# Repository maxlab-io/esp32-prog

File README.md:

# esp32-prog

A compact USB‑C programmer for flashing and debugging ESP32‑based boards over UART, designed to connect to the target through a [Tag‑Connect TC2050‑IDC](https://www.tag-connect.com/product/tc2050-idc-tag-connect-2050-idc) cable so the target board needs no programming header at all.

Plug it into USB, press the Tag‑Connect onto the target, and flash with `esptool`, ESP‑IDF, Arduino or PlatformIO. The on‑board auto‑reset circuit puts the ESP32 into download mode automatically, with no BOOT/EN buttons to press.

## Features

- **USB‑C** (USB 2.0) with 5.1 kΩ CC pull‑downs, so it works with both C‑to‑C and A‑to‑C cables
- **CP2102** USB‑to‑UART bridge
- **Automatic boot/reset**: the standard Espressif DTR/RTS cross‑coupled circuit, built with AO3400A MOSFETs
- **Switchable target power**: independent 5 V and 3.3 V outputs, each enabled by a DIP switch
- **3.3 V LDO** (ST LD39200, 2 A class) for powering the target
- **Buffered, back‑power‑safe I/O**: SN74LVC1G125 buffers with I<sub>off</sub> protection, so an unpowered target is not parasitically powered through its UART or strapping pins
- **ESD protection** on VBUS, D+ and D‑, plus a ferrite bead on VBUS
- **Status LEDs** for USB power, 5 V out, 3.3 V present, TX and RX activity
- 2‑layer, 55 × 30 mm board, four M3 mounting holes, all components on the top side

## Connector pinout

The target connector **J2** is a 2×5, 2.54 mm pin header that mates with the 0.1" IDC end of a Tag‑Connect TC2050‑IDC cable. The pinout is also printed on the board silkscreen.

| Pin | Silkscreen | Signal | Direction (from programmer) | Connect to on target |
|----:|:----------:|--------|-----------------------------|----------------------|
| 1 | 5V   | +5V     | Power out (switched)     | 5 V / VIN (optional) |
| 2 | 3V3  | +3.3V   | Power out (switched) / I/O reference | 3V3 rail (**always connect**, see below) |
| 3 | GND  | GND     | n/a                      | GND |
| 4 | GND  | GND     | n/a                      | GND |
| 5 | EN   | ESP_EN  | Open‑drain, pulls low    | `EN` / `CHIP_PU` |
| 6 | BT   | ESP_BOOT| Open‑drain, pulls low    | Boot strapping pin (`GPIO0` on ESP32/S2/S3, `GPIO9` on C3/C6/H2) |
| 7 | RX   | RXD     | Input                    | Target `U0TXD` |
| 8 | TX   | TXD     | Output                   | Target `U0RXD` |
| 9 | NC   | n/a     | Not connected            | n/a |
| 10 | NC  | n/a     | Not connected            | n/a |

TX and RX are named from the programmer's point of view, so they cross over to the target's UART.

### Designing the target‑side footprint

- Use the **TC2050** footprint (the legged version, to match the TC2050‑IDC cable's retaining clips) and assign signals using the pin numbers in the table above.
- **Always route pin 2 to the target's 3.3 V rail**, even if the target has its own supply. The TX, EN and BOOT buffers are powered from this pin, so it sets the output logic level and lets the programmer work with self‑powered targets.
- EN and BOOT are only ever pulled low by the programmer, so the target must provide its own pull‑ups (most ESP32 modules and reference designs already have them).

## Using it

### Power switch and LEDs

The two‑position DIP switch **SW1** (labeled `5V` and `3.3V` on the silkscreen) enables the corresponding output on J2.

| Target situation | 5V | 3.3V |
|------------------|:--:|:----:|
| Target has its own power supply | Off | Off |
| Power the target from the programmer, 3.3 V only | Off | On |
| Power the target from the programmer, through its own 5 V regulator | On | Off |

Do not enable an output when the target is already powered from another source. Both outputs pass through SS34 Schottky diodes to prevent back‑feeding into the programmer, so expect a few hundred millivolts of drop under load.

| LED | Color | Meaning |
|-----|-------|---------|
| D5  | Red   | USB power present |
| D4  | Red   | 5 V output enabled |
| D8  | Red   | 3.3 V present on J2 pin 2 (from the programmer or the target) |
| D9  | Blue  | TX activity |
| D10 | Blue  | RX activity |

### Drivers

Linux supports the CP2102 out of the box (`cp210x` driver), and the programmer shows up as `/dev/ttyUSB*`. On Windows or macOS, if no serial port appears, install the [Silicon Labs CP210x VCP driver](https://www.silabs.com/developer-tools/usb-to-uart-bridge-vcp-drivers).

### Flashing

Because DTR and RTS drive the auto‑reset circuit, any tool that uses esptool's default reset sequence works without touching the target:

```sh
# ESP-IDF
idf.py -p /dev/ttyUSB0 flash monitor

# esptool directly: quick sanity check that the target is reachable
esptool.py --port /dev/ttyUSB0 flash_id
```

Arduino IDE and PlatformIO use esptool under the hood, so selecting the programmer's serial port is all that is needed.

## How it works

1. **USB input.** USB‑C VBUS passes through a ferrite bead (BLM21PG221SN1D). RClamp0521P TVS diodes protect VBUS, D+ and D‑.
2. **USB‑UART.** A CP2102‑GMR, powered from VBUS through its internal regulator, provides TXD/RXD plus the DTR and RTS modem lines.
3. **Auto‑reset.** DTR and RTS are buffered and fed to two cross‑coupled AO3400A N‑MOSFETs, the same topology as on Espressif DevKits. Toggling DTR/RTS pulls EN and BOOT low in the sequence that esptool expects.
4. **Target power.** An LD39200 LDO generates 3.3 V from VBUS. Two AO3401A P‑MOSFETs, enabled by SW1, switch VBUS and the 3.3 V rail onto J2 through SS34 Schottky diodes.
5. **Level handling.** The TX, DTR and RTS buffers (SN74LVC1G125) run from J2 pin 2, so they follow the target's supply voltage. When the target is unpowered, their I<sub>off</sub> feature keeps the outputs high‑impedance, so the target is not back‑powered. The RX buffer runs from VBUS so it is always ready to receive.

Design notes and references are included directly on the schematic.

## Opening the design

The project is made with **KiCad 7**.

| File | Contents |
|------|----------|
| `esp32-prog.kicad_pro` | KiCad project |
| `esp32-prog.kicad_sch` | Schematic |
| `esp32-prog.kicad_pcb` | PCB layout |
| `sym-lib-table`, `fp-lib-table` | Project library tables (KIML) |
| `fab/` | Manufacturing outputs (see below) |

Symbols and footprints come from **[KIML](https://github.com/maxlab-io/kiml)**, MAXLAB's KiCad library, in which every part carries its manufacturer part number and supplier links. Footprints are embedded in the PCB and symbols are cached in the schematic, so the project opens without KIML, but to edit or update parts:

1. Clone the library: `git clone https://github.com/maxlab-io/kiml.git`
2. In KiCad, go to **Preferences → Configure Paths** and add a variable named `KIML_ROOT` pointing to the cloned directory.

The project's library tables already reference `${KIML_ROOT}`, so nothing else needs configuring.

## Manufacturing

Ready‑to‑order outputs are in `fab/generic/`:

| File | Contents |
|------|----------|
| `esp32_prog_generic_gerbs.zip` | Gerbers, drill files and drill maps |
| `esp32_prog_generic_bom.zip` | BOM grouped by value, with manufacturer and supplier part numbers |
| `esp32_prog_generic_pos.zip` | Component placement file (KiCad format) |

Board specs: 2 layers, 1.6 mm, 55 × 30 mm. All parts are on the top side, so single‑sided assembly is enough. Hand assembly is possible but fiddly, given 0402 passives, a QFN‑28 and 1 × 1.45 mm USON‑6 buffers.

Every part in the BOM has an MPN and a JLCPCB/LCSC part number, so it can be sourced from JLCPCB/LCSC as is. To order assembly from JLCPCB, rename the BOM and placement columns to match JLCPCB's upload format, and check part rotations in their preview before confirming the order.

### Regenerating the outputs

1. In the PCB editor, export Gerbers and drill files into `fab/generic/gerbs/`, the BOM into `fab/generic/bom/`, and the placement file into `fab/generic/pos/`.
2. Run the packaging script:

   ```sh
   cd fab/generic
   ./fab_pack.sh
   ```

The script re‑creates the zip archives. Loose `.csv` files are ignored by git, so the BOM and placement files are committed only inside the zips.

## Key components

| Ref | Part | Function | JLCPCB # |
|-----|------|----------|----------|
| U2 | Silicon Labs CP2102‑GMR | USB‑to‑UART bridge | C6568 |
| U1 | ST LD39200DPUR | 3.3 V LDO | C880590 |
| U3–U6 | TI SN74LVC1G125DRYR | Buffers with I<sub>off</sub> | C527546 |
| Q1, Q2 | AO3401A | Power switches (P‑MOSFET) | C15127 |
| Q3, Q4 | AO3400A | Auto‑reset (N‑MOSFET) | C20917 |
| D6, D7 | SS34 | Back‑feed protection | C266553 |
| D1–D3 | RCLAMP0521P‑N | USB ESD protection | C316043 |
| J1 | HRO TYPE‑C‑31‑M‑12 | USB‑C receptacle | C165948 |
| J2 | HCTL PZ254‑2‑05‑Z‑8.5 | 2×5 2.54 mm header | C2894966 (LCSC) |
| SW1 | Yuandi TP‑02 | Power‑select DIP switch | C559165 |

The complete BOM is in `fab/generic/esp32_prog_generic_bom.zip`.

## License

<!-- TODO: choose a license, e.g. CERN-OHL-P/S/W for hardware, and add a LICENSE file. -->

No license has been chosen for this project yet.

---

Designed by [MAXLAB.IO](https://github.com/maxlab-io).

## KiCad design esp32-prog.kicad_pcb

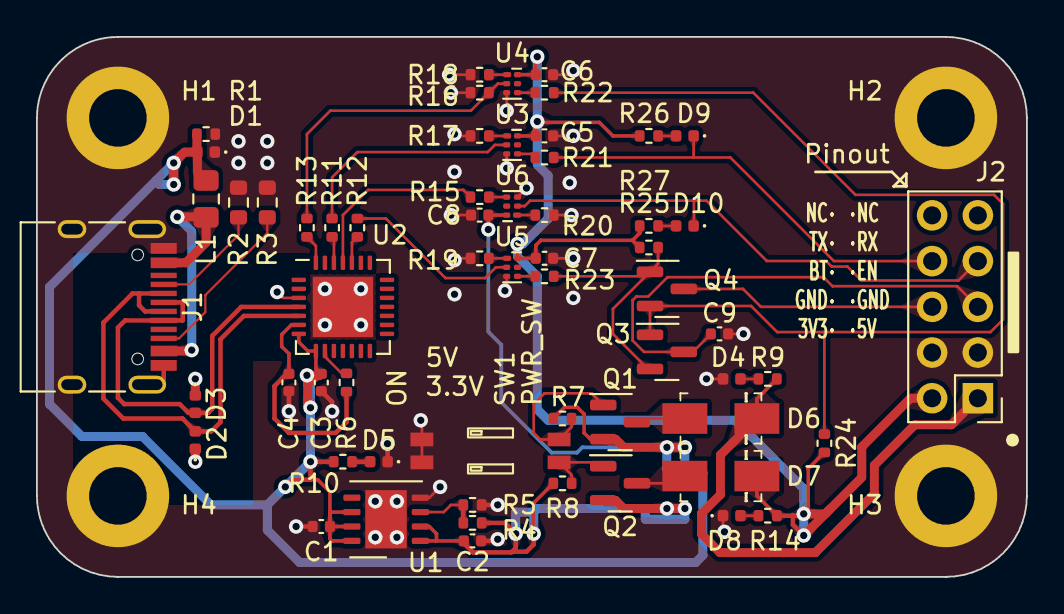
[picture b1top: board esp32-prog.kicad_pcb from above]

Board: 2 copper layers, 55.0 x 30.0 mm, 64 parts (0 on the bottom side), 43 nets.

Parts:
C1, C2, C3, C4, C5, C6, C7, C8, C9: 10u_0402_LDK105CBJ106MVLF; C_0402_1005Metric
D1, D2, D3: SOD-882_0402_RCLAMP0521P-N; D_0402_1005Metric
D4, D5, D8: 0402_RED_16-213SDRC/S530-A3/TR8; LED_0402_1005Metric
D6, D7: SS34; DO-214AC
D9, D10: 0402_BLUE_NCD0402B1; LED_0402_1005Metric
H1, H2, H3, H4: MH; MountingHole_3.2mm_M3_ISO7380_Pad
J1: TYPE-C-31-M-12; USB_C_Receptacle_HRO_TYPE-C-31-M-12
J2: Conn-02x05_PZ254-2-05-Z-8.5; PinHeader_2x05_P2.54mm_Vertical
L1: FB_2A_0805_220R@100MHz_BLM21PG221SN1D; L_0805_2012Metric_Pad1.15x1.40mm_HandSolder
Q1, Q2: AO3401A; SOT-23
Q3, Q4: AO3400A; SOT-23
R1, R5, R6, R7, R8, R16, R17, R18, R19, R20, R24, R25: 10k_0402_0402WGF1002TCE; R_0402_1005Metric
R2, R3: 5.1k_0603_0603WAF5101T5E; R_0603_1608Metric
R4: 56k_0402_ERJ2RKF5602X; R_0402_1005Metric
R9, R10, R14, R26, R27: 1k_0402_0402WGF1001TCE; R_0402_1005Metric
R11, R12, R13, R15, R21, R22, R23: 32.4R_0402_AC0402FR-0732R4L; R_0402_1005Metric
SW1: SW_DIP_x02_50mil_1.27mm_TP-02; SW_DIP_1.27mm_0.50mil_TP-02
U1: LD39200DPUR; DFN-8-1EP_4x4mm_P0.8mm_EP2.3x3.24mm
U2: CP2102-GMR; QFN-28-1EP_5x5mm_P0.5mm_EP3.35x3.35mm
U3, U4, U5, U6: TI_SN74LVC1G125DRYR; Texas_USON-6_1x1.45mm_P0.5mm_SMD

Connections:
+3.3V: C5.1, C6.1, C7.1, D7.K, J2.2, R14.1, R24.1, R25.1, R26.1, R27.1, U3.6 (V), U4.6 (V), U5.6 (V)
+3.3VA: C2.2, Q2.2 (S), R4.1, R8.1, U1.1 (OUT), U1.2 (OUT)
+5V: D6.K, J2.1, R9.1
/ESP_BOOT: J2.6, Q4.3 (D)
/ESP_EN: C9.1, J2.5, Q3.3 (D)
/RXD: D10.1 (K), J2.7, U6.2
/TXD: D9.1 (K), J2.8, R21.2
/UD+: D3.2 (A2), J1.A6 (D+), J1.B6 (D+), U2.4 (D+)
/UD-: D2.2 (A2), J1.A7 (D-), J1.B7 (D-), U2.5 (D-)
GND: C1.1, C2.1, C3.2, C4.2, C5.2, C6.2, C7.2, C8.2, C9.2, D1.1 (A1), D2.1 (A1), D3.1 (A1), D4.1 (K), D5.1 (K), D8.1 (K), H1.1, H2.1, H3.1, H4.1, J1.A1 (GND), J1.A12 (GND), J1.B1 (GND), J1.B12 (GND), J1.S1 (SHIELD), J2.3, J2.4, R1.2, R2.2, R3.2, R5.2, R16.1, R17.2, R18.2, R19.2, R20.2, SW1.1, SW1.2, U1.4 (GND), U1.9 (PAD), U2.3 (GND), U2.29 (GND), U3.3 (G), U4.3 (G), U5.3 (G), U6.3 (G)
unnamed: D4.2 (A), R9.2
unnamed: D5.2 (A), R10.2
unnamed: D8.2 (A), R14.2
unnamed: D9.2 (A), R26.2
unnamed: D10.2 (A), R27.2
unnamed: J1.A5 (CC1), R2.1
unnamed: J1.B5 (CC2), R3.1
unnamed: J1.A4 (VBUS), J1.A9 (VBUS), J1.B4 (VBUS), J1.B9 (VBUS), L1.1
unnamed: D6.A, Q1.3 (D)
unnamed: Q1.1 (G), R7.2, SW1.4
unnamed: D7.A, Q2.3 (D)
unnamed: Q2.1 (G), R8.2, SW1.3
unnamed: Q3.1 (G), Q4.2 (S), R22.2, R24.2
unnamed: Q3.2 (S), Q4.1 (G), R23.2, R25.2
unnamed: R11.2, U3.2
unnamed: R12.2, U5.2
unnamed: R13.2, R16.2, U4.2
unnamed: R15.2, U6.4
unnamed: R17.1, U3.1
unnamed: R18.1, U4.1
unnamed: R19.1, U5.1
unnamed: R20.1, U6.1
unnamed: R21.1, U3.4
unnamed: R22.1, U4.4
unnamed: R23.1, U5.4
unnamed: R4.2, R5.1, U1.3 (ADJ)
unnamed: R15.1, U2.25 (RXD)
unnamed: R11.1, U2.26 (TXD)
unnamed: C4.1, R6.2, U2.6 (VDD)
unnamed: R13.1, U2.28 (~DTR)
unnamed: R6.1, U2.9 (~RST)
unnamed: R12.1, U2.24 (~RTS)
VBUS: C1.2, C3.1, C8.1, D1.2 (A2), L1.2, Q1.2 (S), R1.1, R7.1, R10.1, U1.6 (EN), U1.7 (IN), U1.8 (IN), U2.7 (VREGIN), U2.8 (VBUS), U6.6 (V)

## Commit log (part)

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2022-11-04 initial commit: gitignore
2022-11-04 draft schematics
2022-11-07 draft schematics complete
2022-11-07 fix DRC in schematics
2022-11-07 begin routing: place all basic blocks
2022-11-08 draft route complete
2022-11-08 draft route: add more gnd guard traces
2022-11-08 draft route: complete, ready for review
2022-11-09 route: addressed R. comments w.r.t. power assign
2022-11-09 route: add fancy silk
2022-11-09 fab: add jlcpcb export
2022-11-09 fab: fix jlcpcb export - cpl file and such
2022-11-09 fab: fix 4.7u cap and buffer FP
2023-07-25 pcb: next revision schematics and prelim routing
2023-08-09 pcb: add markings for the tag connector and pwr switch
2023-08-09 fab: preparing rev2 files
2024-07-16 address the incorect pinout of the LD39200DPUR
